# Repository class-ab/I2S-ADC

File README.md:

# I2S-ADC

DIY analogue-digital converter for audio recording using I2S and a microcontoller, written to an SD card and/or USB-C. Designed to be low cost, highly portable (battery powered) but also usable as an USB audio interface.

AI declaration:

AI such as ChatGPT and Claude was used in the development of this system, such as through research, understanding content and coding. All designs are my own.

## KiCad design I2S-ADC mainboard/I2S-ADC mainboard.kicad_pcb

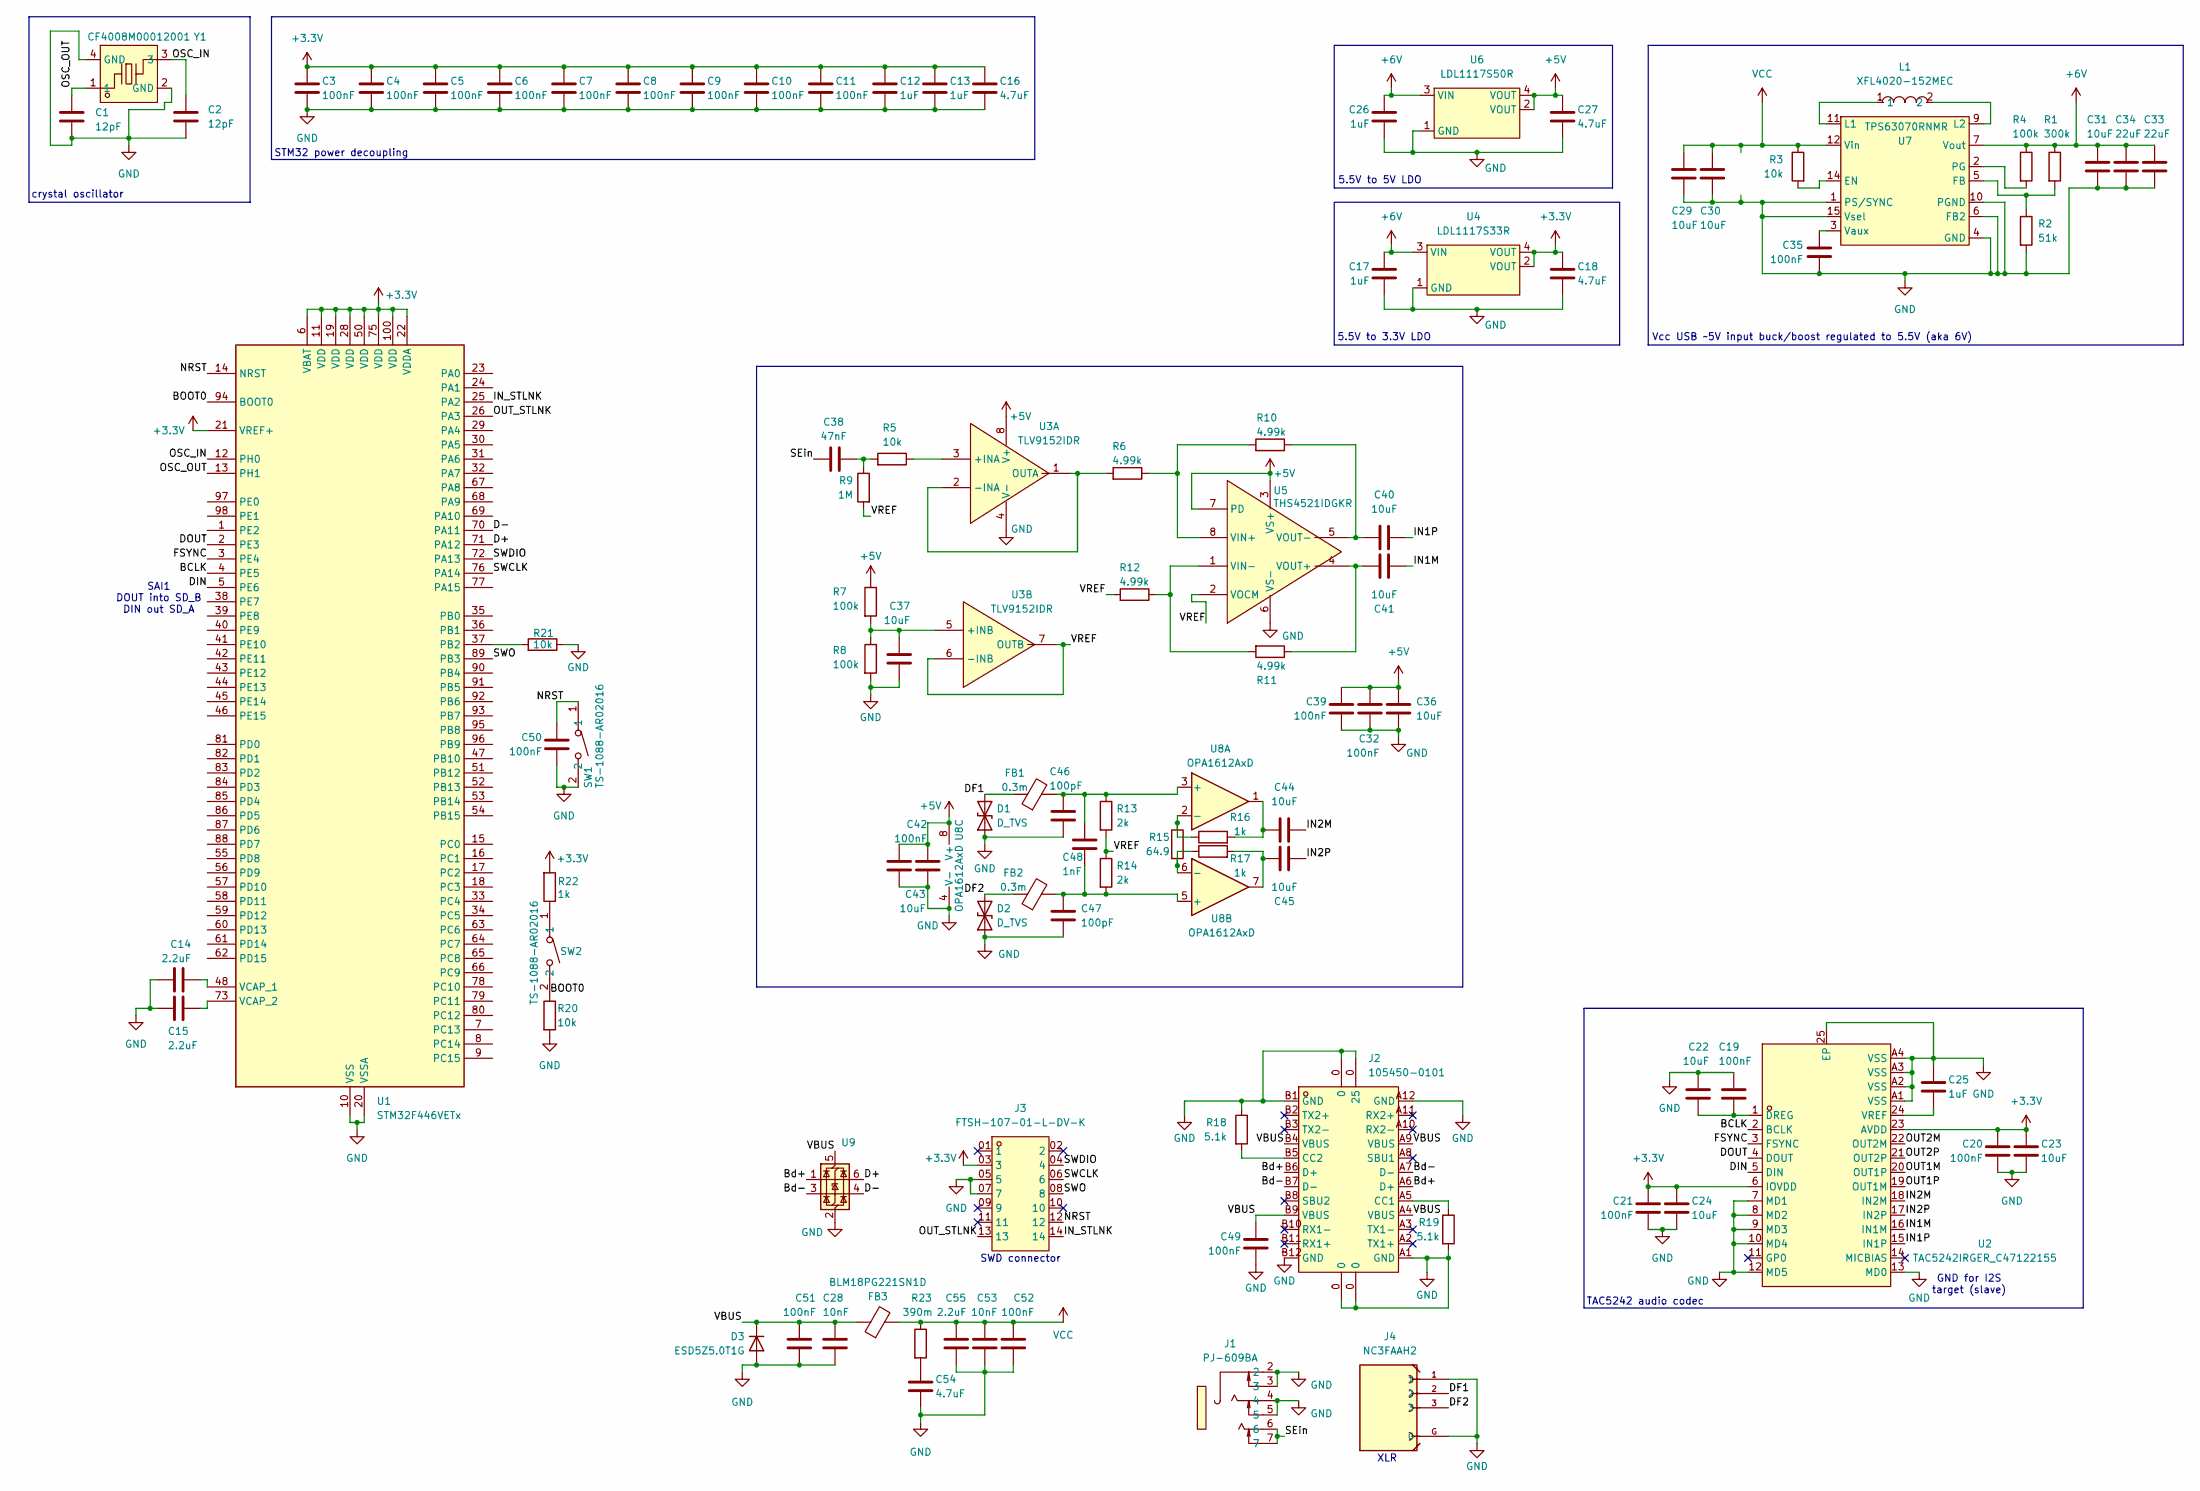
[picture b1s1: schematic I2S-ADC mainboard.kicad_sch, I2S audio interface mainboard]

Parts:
C1, C2: 12pF; C_0603_1608Metric
C3, C4, C5, C6, C7, C8, C9, C10, C11, C19, C20, C21, C32, C39, C42, C49, C50, C51, C52: 100nF; C_0603_1608Metric
C12, C13, C17, C25, C26: 1uF; C_0603_1608Metric
C14, C15: 2.2uF; C_0603_1608Metric
C16, C18, C27, C54: 4.7uF; C_0603_1608Metric
C22, C23, C24, C30, C31, C36, C37, C43: 10uF; C_0603_1608Metric
C28, C53: 10nF; C_0805_2012Metric
C29: 10uF; C_0805_2012Metric
C33, C34: 22uF; C_0805_2012Metric
C35: 100nF; C_0402_1005Metric
C38: 47nF; C_1206_3216Metric
C40, C41, C44, C45: 10uF; C_Rect_L18.0mm_W11.0mm_P15.00mm_FKS3_FKP3
C46, C47: 100pF; C_0603_1608Metric
C48: 1nF; C_0603_1608Metric
C55: 2.2uF; C_0805_2012Metric
D1, D2: D_TVS; D_SOD-523
D3: ESD5Z5.0T1G; D_SOD-523
FB1, FB2: 0.3m; L_0805_2012Metric
FB3: BLM18PG221SN1D; L_0603_1608Metric
J1: PJ-609BA; AUDIO-TH_PJ-609BA; MPN PJ-609BA; LCSC Part C309277
J2: 105450-0101; USB-C-SMD_TYPE-C-USB-18; MPN 1054500101; LCSC Part C134092
J3: FTSH-107-01-L-DV-K; HDR-SMD_14P-P1.27_FTSH-107-01-L-DV-K; MPN FTSH-107-01-L-DV-K; LCSC Part C5307809
J4: NC3FAAH2; NEUTRIK_NC3FAAH2; MPN NC3FAAH2
L1: XFL4020-152MEC; IND-SMD_L4.0-W4.0-A; MPN XFL4020-152MEC; LCSC Part C3033018
R1: 300k; R_0603_1608Metric
R2: 51k; R_0603_1608Metric
R3, R5, R20, R21: 10k; R_0603_1608Metric
R4, R7, R8: 100k; R_0603_1608Metric
R6, R10, R11, R12: 4.99k; R_0603_1608Metric
R9: 1M; R_0603_1608Metric
R13, R14: 2k; R_0603_1608Metric
R15: 64.9; R_0603_1608Metric
R16, R17, R22: 1k; R_0603_1608Metric
R18, R19: 5.1k; R_0603_1608Metric
R23: 390m; R_0603_1608Metric
SW1, SW2: TS-1088-AR02016; SW-SMD_L3.9-W3.0-P4.45; MPN TS-1088-AR02016; LCSC Part C720477
U1: STM32F446VETx; LQFP-100_14x14mm_P0.5mm
U2: TAC5242IRGER_C47122155; VQFN-24_L4.0-W4.0-P0.50-BL-EP2.1_1; MPN TAC5242IRGER; LCSC Part C47122155
U3: TLV9152IDR; SOIC-8_L4.9-W3.9-P1.27-LS6.0-BL; MPN TLV9152IDR; LCSC Part C882649
U4: LDL1117S33R; SOT-223-4_L6.5-W3.5-P2.30-LS7.0-BR; MPN LDL1117S33R; LCSC Part C435835
U5: THS4521IDGKR; VSSOP-8_L3.0-W3.0-P0.65-LS5.0-BL; MPN THS4521IDGKR; LCSC Part C170157
U6: LDL1117S50R; SOT-223-3_L6.5-W3.4-P2.30-LS7.0-BR; MPN LDL1117S50R; LCSC Part C970558
U7: TPS63070RNMR; VQFN-15_L3.0-W2.5-P0.50-BL; MPN TPS63070RNMR; LCSC Part C109322
U8: OPA1612AxD; SOIC-8_3.9x4.9mm_P1.27mm
U9: USBLC6-2SC6; SOT-23-6
Y1: CF4008M00012001; CRYSTAL-SMD_4P-L3.2-W2.5-BL_SIT8008BI; MPN CF4008M00012001; LCSC Part C7294546

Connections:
+3.3V: C3.1, C4.1, C5.1, C6.1, C7.1, C8.1, C9.1, C10.1, C11.1, C12.1, C13.1, C16.1, C18.1, C20.1, C21.1, C23.1, C24.1, J3.03 (3), R22.2, U1.6 (VBAT), U1.11 (VDD), U1.19 (VDD), U1.21 (VREF+), U1.22 (VDDA), U1.28 (VDD), U1.50 (VDD), U1.75 (VDD), U1.100 (VDD), U2.6 (IOVDD), U2.23 (AVDD), U4.2 (VOUT), U4.4 (VOUT)
+5V: C27.1, C32.1, C36.1, C39.1, C42.1, C43.1, R7.1, U3.8 (V+), U5.3 (VS+), U5.7 (PD), U6.2 (VOUT), U6.4 (VOUT), U8.8 (V+)
+6V: C17.1, C26.1, C31.1, C33.1, C34.1, R1.1, R4.1, U4.3 (VIN), U6.3 (VIN), U7.7 (Vout)
/BCLK: U1.4 (PE5), U2.2 (BCLK)
/BOOT0: R20.1, SW2.2, U1.94 (BOOT0)
/Bd+: J2.A6 (D+), J2.B6 (D+), U9.1 (I/O1)
/Bd-: J2.A7 (D-), J2.B7 (D-), U9.3 (I/O2)
/D+: U1.71 (PA12), U9.6 (I/O1)
/D-: U1.70 (PA11), U9.4 (I/O2)
/DF1: D1.2 (A2), FB1.1, J4.2
/DF2: D2.2 (A2), FB2.1, J4.3
/DIN: U1.5 (PE6), U2.5 (DIN)
/DOUT: U1.2 (PE3), U2.4 (DOUT)
/FSYNC: U1.3 (PE4), U2.3 (FSYNC)
/IN1M: C41.2, U2.16 (IN1M)
/IN1P: C40.2, U2.15 (IN1P)
/IN2M: C44.2, U2.18 (IN2M)
/IN2P: C45.2, U2.17 (IN2P)
/IN_STLNK: J3.14, U1.25 (PA2)
/NRST: C50.1, J3.12, SW1.1, U1.14 (NRST)
/OSC_IN: C2.1, U1.12 (PH0), Y1.3
/OSC_OUT: C1.1, U1.13 (PH1), Y1.1
/OUT1M: U2.20 (OUT1P)
/OUT1P: U2.19 (OUT1M)
/OUT2M: U2.22 (OUT2M)
/OUT2P: U2.21 (OUT2P)
/OUT_STLNK: J3.13, U1.26 (PA3)
/SEin: C38.1, J1.6, J1.7
/SWCLK: J3.06 (6), U1.76 (PA14)
/SWDIO: J3.04 (4), U1.72 (PA13)
/SWO: J3.08 (8), U1.89 (PB3)
/VBUS: C28.1, C49.1, C51.1, D3.1 (K), FB3.1, J2.A4 (VBUS), J2.A9 (VBUS), J2.B4 (VBUS), J2.B9 (VBUS), U9.5 (VBUS); also elsewhere on the board
/VREF: R9.2, R12.2, R13.2, R14.1, U3.6 (-INB), U3.7 (OUTB), U5.2 (VOCM)
GND: C1.2, C2.2, C3.2, C4.2, C5.2, C6.2, C7.2, C8.2, C9.2, C10.2, C11.2, C12.2, C13.2, C14.2, C15.2, C16.2, C17.2, C18.2, C19.1, C20.2, C21.2, C22.1, C23.2, C24.2, C25.1, C26.2, C27.2, C28.2, C29.2, C30.2, C31.2, C32.2, C33.2, C34.2, C35.2, C36.2, C37.2, C39.2, C42.2, C43.2, C46.2, C47.2, C49.2, C50.2, C51.2, C52.2, C53.2, C54.2, C55.2, D1.1 (A1), D2.1 (A1), D3.2 (A), J1.2, J1.3, J1.4, J1.5, J2.0, J2.A1 (GND), J2.A12 (GND), J2.B1 (GND), J2.B12 (GND), J3.05 (5), J3.07 (7), J4.1, J4.G, R2.2, R8.2, R18.1, R19.2, R20.2, R21.1, SW1.2, U1.10 (VSS), U1.20 (VSSA), U1.27 (VSS), U1.49 (VSS), U1.74 (VSS), U1.99 (VSS), U2.7 (MD1), U2.8 (MD2), U2.9 (MD3), U2.10 (MD4), U2.12 (MD5), U2.13 (MD0), U2.25 (EP), U2.A1 (VSS), U2.A2 (VSS), U2.A3 (VSS), U2.A4 (VSS), U3.4 (V-), U4.1 (GND), U5.6 (VS-), U6.1 (GND), U7.1 (PS/SYNC), U7.4 (GND), U7.6 (FB2), U7.10 (PGND), U7.15 (Vsel), U8.4 (V-), U9.2 (GND), Y1.2 (GND), Y1.4 (GND); also elsewhere on the board
unnamed: C38.2, R5.2, R9.1
unnamed: C44.1, R16.2, U8.1
unnamed: C45.1, R17.2, U8.7
unnamed: C54.1, R23.2
unnamed: J2.A5 (CC1), R19.1
unnamed: J2.B5 (CC2), R18.2
unnamed: R22.1, SW2.1
unnamed: R21.2, U1.37 (PB2)
unnamed: C14.1, U1.48 (VCAP_1)
unnamed: C15.1, U1.73 (VCAP_2)
unnamed: C19.2, C22.2, U2.1 (DREG)
unnamed: C25.2, U2.24 (VREF)
unnamed: R5.1, U3.3 (+INA)
unnamed: R6.2, U3.1 (OUTA), U3.2 (-INA)
unnamed: C37.1, R7.2, R8.1, U3.5 (+INB)
unnamed: R6.1, R10.2, U5.8 (VIN+)
unnamed: R11.2, R12.1, U5.1 (VIN-)
unnamed: C41.1, R11.1, U5.4 (VOUT+)
unnamed: C40.1, R10.1, U5.5 (VOUT-)
unnamed: R3.2, U7.14 (EN)
unnamed: R1.2, R2.1, U7.5 (FB)
unnamed: L1.1, U7.11 (L1)
unnamed: L1.2, U7.9 (L2)
unnamed: R4.2, U7.2 (PG)
unnamed: C35.1, U7.3 (Vaux)
unnamed: C46.1, C48.1, FB1.2, R13.1, U8.3 (+)
unnamed: R15.1, R16.1, U8.2 (-)
unnamed: C47.1, C48.2, FB2.2, R14.2, U8.5 (+)
unnamed: R15.2, R17.1, U8.6 (-)
VCC: C29.1, C30.1, C52.1, C53.1, C55.1, FB3.2, R3.1, R23.1, U7.12 (Vin)

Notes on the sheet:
SWD connector
XLR
Vcc USB ~5V input buck/boost regulated to 5.5V (aka 6V)
TAC5242 audio codec
STM32 power decoupling
SAI1 DOUT into SD_B DIN out SD_A
GND for I2S target (slave)
5.5V to 5V LDO
crystal oscillator
5.5V to 3.3V LDO

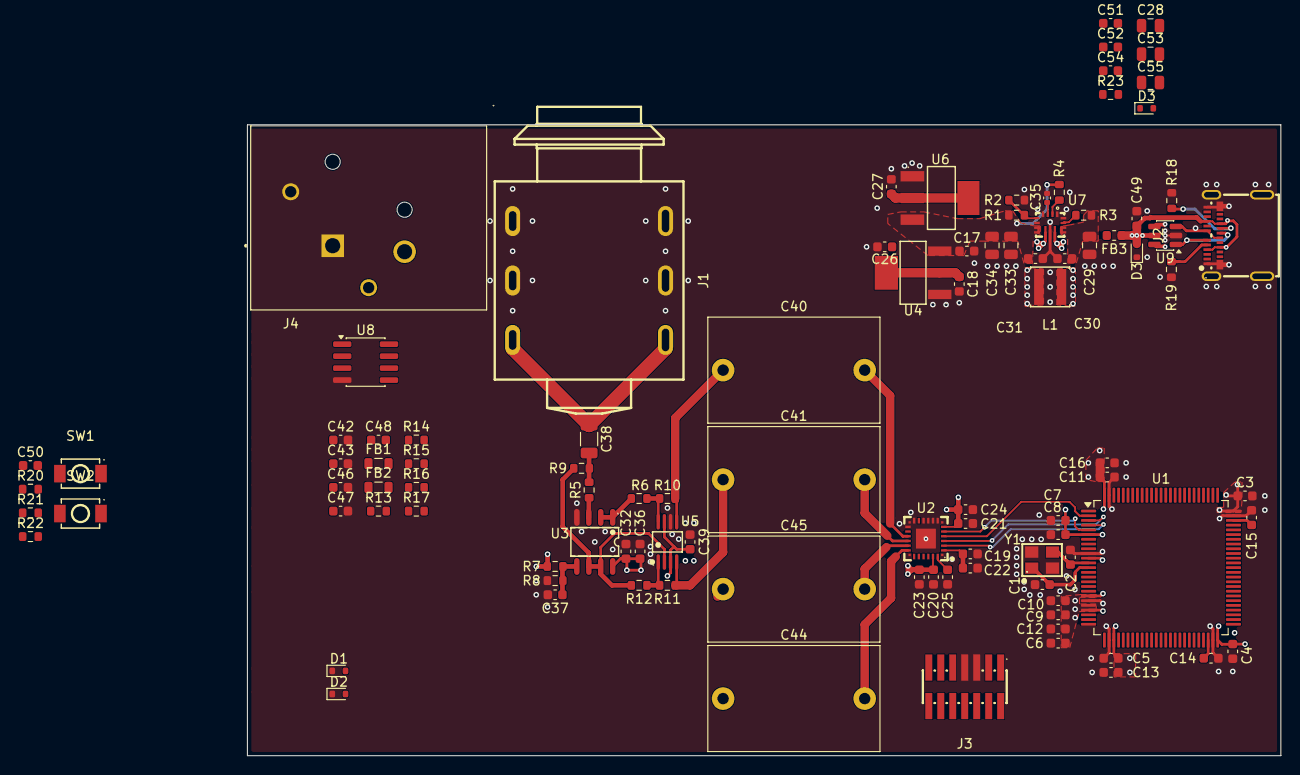
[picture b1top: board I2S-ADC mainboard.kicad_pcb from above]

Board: 4 copper layers, 109.5 x 66.8 mm, 102 parts (0 on the bottom side), 60 nets.

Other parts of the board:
D3#2: D_TVS; D_SOD-523

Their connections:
/VBUS: D3#2.2 (A2); also elsewhere on the board
GND: D3#2.1 (A1); also elsewhere on the board

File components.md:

easyeda2kicad --full --lcsc_id=Cx --output  C:\Users\aiden\Documents\GitHub\kicad-parts\easyeda2kicad

# MCU

**U1: STM32F446VET6**

- JLC: https://jlcpcb.com/partdetail/STMicroelectronics-STM32F446VE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 

- Datasheet: https://www.st.com/content/ccc/resource/technical/document/d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 

#### Power:

**C3-11, C19-21, C32, C39, C42, C49-50:** https://jlcpcb.com/partdetail/YAGEO-CC0603KRX7R9BB104/C14663 (100nF)

- decoupling caps for 9x VDD (+VBAT, VDDA, VREF+), 3x AVDD, DREG, IOVDD, 1x TLV9152

**C12-13, C17, C25-26:** https://jlcpcb.com/partdetail/16531-CL10A105KB8NNNC/C15849 (1uF)

- decoupling caps for STM32, LDL1117S33R and LDL1117S50R  

**C14-15:** https://jlcpcb.com/partdetail/24366-CL10A225KO8NNNC/C23630 (2.2uF)

- caps for STM32 internal regulator VCAP_1 and VCAP_2 

**C16, C18, C27:** https://jlcpcb.com/partdetail/20375-CL10A475KO8NNNC/C19666 (4.7uF)

- bulk decoupling caps for STM32, LDL1117S33R and LDL1117S50R

**SW1-3:** https://jlcpcb.com/partdetail/XUNPU-TS_1088AR02016/C720477

#### Crystal oscillator + capacitors

**Y1:** CF4008M00012001

- JLC: https://jlcpcb.com/partdetail/huaxindianzi-CF4008M00012001/C7294546

- 8 MHz frequency

- 12pF load capacitance

- 40 ohm ESR

**C1, C2:** CC0603FRNPO9BN120

- JLC: https://jlcpcb.com/partdetail/YAGEO-CC0603FRNPO9BN120/C519482

- 12pF capacitance

- NP0 rating, plus/minus 1%

- 0603 footprint

# Audio codec

**U2:** TAC5242

- JLC: https://jlcpcb.com/partdetail/TexasInstruments-TAC5242IRGER/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

- Datasheet: https://www.ti.com/lit/ds/symlink/tac5242.pdf

**C22-24, C30-31, C36-37, C43:** https://jlcpcb.com/partdetail/97651-CL10A106MA8NRNC/C96446 (10uF)

- decoupling caps for TAC5242, TPS63070 and TLV9152

# Audio buffer/filter

**U3:** TLV9152

- JLC: https://jlcpcb.com/partdetail/TexasInstruments-TLV9152IDR/C882649

- Datasheet: https://www.ti.com/lit/ds/symlink/tlv9152.pdf

**U5:** THS4521IDGKR

- JLC: https://jlcpcb.com/partdetail/TexasInstruments-THS4521IDGKR/C170157

- Datasheet: https://www.ti.com/lit/ds/symlink/ths4521.pdf

**R9:** https://jlcpcb.com/partdetail/YAGEO-RT0603BRD071ML/C326730 (1M)

**C38:** https://jlcpcb.com/partdetail/MurataElectronics-GRM31M5C1H47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 (47nF 1206)

**R6, R10-12:** https://jlcpcb.com/partdetail/YAGEO-RT0603BRD074K99L/C723532 (4.99k)

**C40-41, C44-45:** https://jlcpcb.com/partdetail/KYET-MEB106K2A1501/C49215602 (10uF film)

**U8:** OPA1612AIDR

- JLC: https://jlcpcb.com/partdetail/TexasInstruments-OPA1612AIDR/C94590

- Datasheet: https://www.ti.com/lit/ds/symlink/opa1612.pdf

**FB1-2:** https://jlcpcb.com/partdetail/Sunlord-GZ2012D601TF/C1017

**D1-2:** https://jlcpcb.com/partdetail/onsemi-ESD5Z33T1G/C61148
**R16-17, R22:** https://jlcpcb.com/partdetail/YAGEO-RT0603BRD071KL/C110776 (1k)

**R13, R14:** https://jlcpcb.com/partdetail/3448513-TC0325B2001T5F/C2989090 (2k)

**R15:** https://jlcpcb.com/partdetail/YAGEO-RT0603BRD0764R9L/C861511 (64.9)

**C46-47:** https://jlcpcb.com/partdetail/546277-GCM1885C2A101FA16D/C527967 (100pF)

**C48:** https://jlcpcb.com/partdetail/YAGEO-CC0603FRNPO9BN102/C309468 (1nF)

# Connectors

**J1:** 6.35mm stereo jack right-angled (PJ-609BA)

- JLC: https://jlcpcb.com/partdetail/HOOYA-PJ609BA/C309277

**J2:** USB-C SMD connector (1054500101)

- JLC: https://jlcpcb.com/partdetail/MOLEX-1054500101/C134092

- Datasheet: https://www.molex.com/content/dam/molex/molex-dot-com/produc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

**J3:** https://jlcpcb.com/partdetail/Samtec-FTSH_107_01_L_DVK/C5307809 SWD - STM32

**J4:** https://jlcpcb.com/partdetail/Neutrik-NC3FAAH2/C368522 XLR

# Power

**U4:** LDL1117S33R

- JLC: https://jlcpcb.com/partdetail/STMicroelectronics-LDL1117S33R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

- Datasheet: https://www.farnell.com/datasheets/2259188.pdf

**U6:** LDL1117S0R 

- JLC: https://jlcpcb.com/partdetail/STMicroelectronics-LDL1117S50R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

- Datasheet: https://www.st.com/content/ccc/resource/technical/document/d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

**U7:** TPS63070RNMR

- JLC: https://jlcpcb.com/partdetail/TexasInstruments-TPS63070RNMR/C109322

- Datasheet: https://www.ti.com/lit/ds/symlink/tps63070.pdf

**L1:** XFL4020-152MEC

- JLC: https://jlcpcb.com/partdetail/Coilcraft-XFL4020152MEC/C3033018 

**C29:** https://jlcpcb.com/partdetail/16532-CL21A106KAYNNNE/C15850 (10uF 0805)

**C33-34:** https://jlcpcb.com/partdetail/46786-CL21A226MAQNNNE/C45783 (22uF)

**C35:** https://jlcpcb.com/partdetail/1877-CL05B104KO5NNNC/C1525 (100nF 0402)

- decoupling caps for TPS63070 (x3 above)

**R1:** https://jlcpcb.com/partdetail/YAGEO-RT0603BRD07300KL/C705762 (300k)

**R2:** https://jlcpcb.com/partdetail/YAGEO-RT0603BRD0751KL/C861458 (51k)

**R3, R5, R20-21:** https://jlcpcb.com/partdetail/YAGEO-RT0603BRD0710KL/C95204 (10k)

**R4, R6-8:** https://jlcpcb.com/partdetail/YAGEO-RT0603BRD07100KL/C122538 (100k)

**R18-19:** https://jlcpcb.com/partdetail/23913-0603WAF5101T5E/C23186 (5.1k)

**U9:** https://jlcpcb.com/partdetail/Stmicroelectronics-USBLC62SC6/C7519

**D3:** https://jlcpcb.com/partdetail/onsemi-ESD5Z50T1G/C82044

**FB3:** https://jlcpcb.com/partdetail/MurataElectronics-BLM18PG121SN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

# Research:

**Audio buffer:**

- OPA1652
  
  - JLC: https://jlcpcb.com/partdetail/TexasInstruments-OPA1652AIDR/C30025
  
  - Datasheet: https://www.ti.com/lit/ds/symlink/opa1652.pdf
  
  - NOT rail-to-rail
  
  - NOT easy to use with single-supply
  
  - Excellent performance etc, but hard to achieve anyway?

- LMC6482
  
  - JLC: https://jlcpcb.com/partdetail/TexasInstruments-LMC6482AIMXNO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
  
  - Datasheet: https://www.ti.com/lit/ds/symlink/lmc6482.pdf?
  
  - IS rail-to-rail
  
  - IS easy to use with single supply
  
  - Mediocre performance, older design

- TLV9152
  
  - JLC: https://jlcpcb.com/partdetail/TexasInstruments-TLV9152IDR/C882649
  
  - Datasheet: https://www.ti.com/lit/ds/symlink/tlv9152.pdf
  
  - IS rail-to-rail (etc)
  
  - Newer design, good performance

**3.3V LDO:**

AMS1117, AP2210, AP2112, ME6231, LM3940, MCP1827, ADM7154, LDL1117

Selected LDL1117 (S33R version = 3.3V output) for:

- Datasheet recommends good ESR ceramic capacitors, compared to other devices asking for specific and expensive tantalum caps etc

- Ultra low noise operation, power supply (input) noise rejection ratio of 87dB

- Cheap and easy to use part
